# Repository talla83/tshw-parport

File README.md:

lsrio16 für Tom simple handwheel -
Eine kleine Erweiterungsplatine mit universellen IOs.

16 x digital output 16 x digital input 

Schnittstelle = Parallel Port oder andere mit GPIO

Der Encoder muss direkt an den ParPort angeschlossen.

http://wiki.linuxcnc.org/cgi-bin/wiki.pl?Shift_Register_Port_Expander

https://www.thingiverse.com/thing:3684937

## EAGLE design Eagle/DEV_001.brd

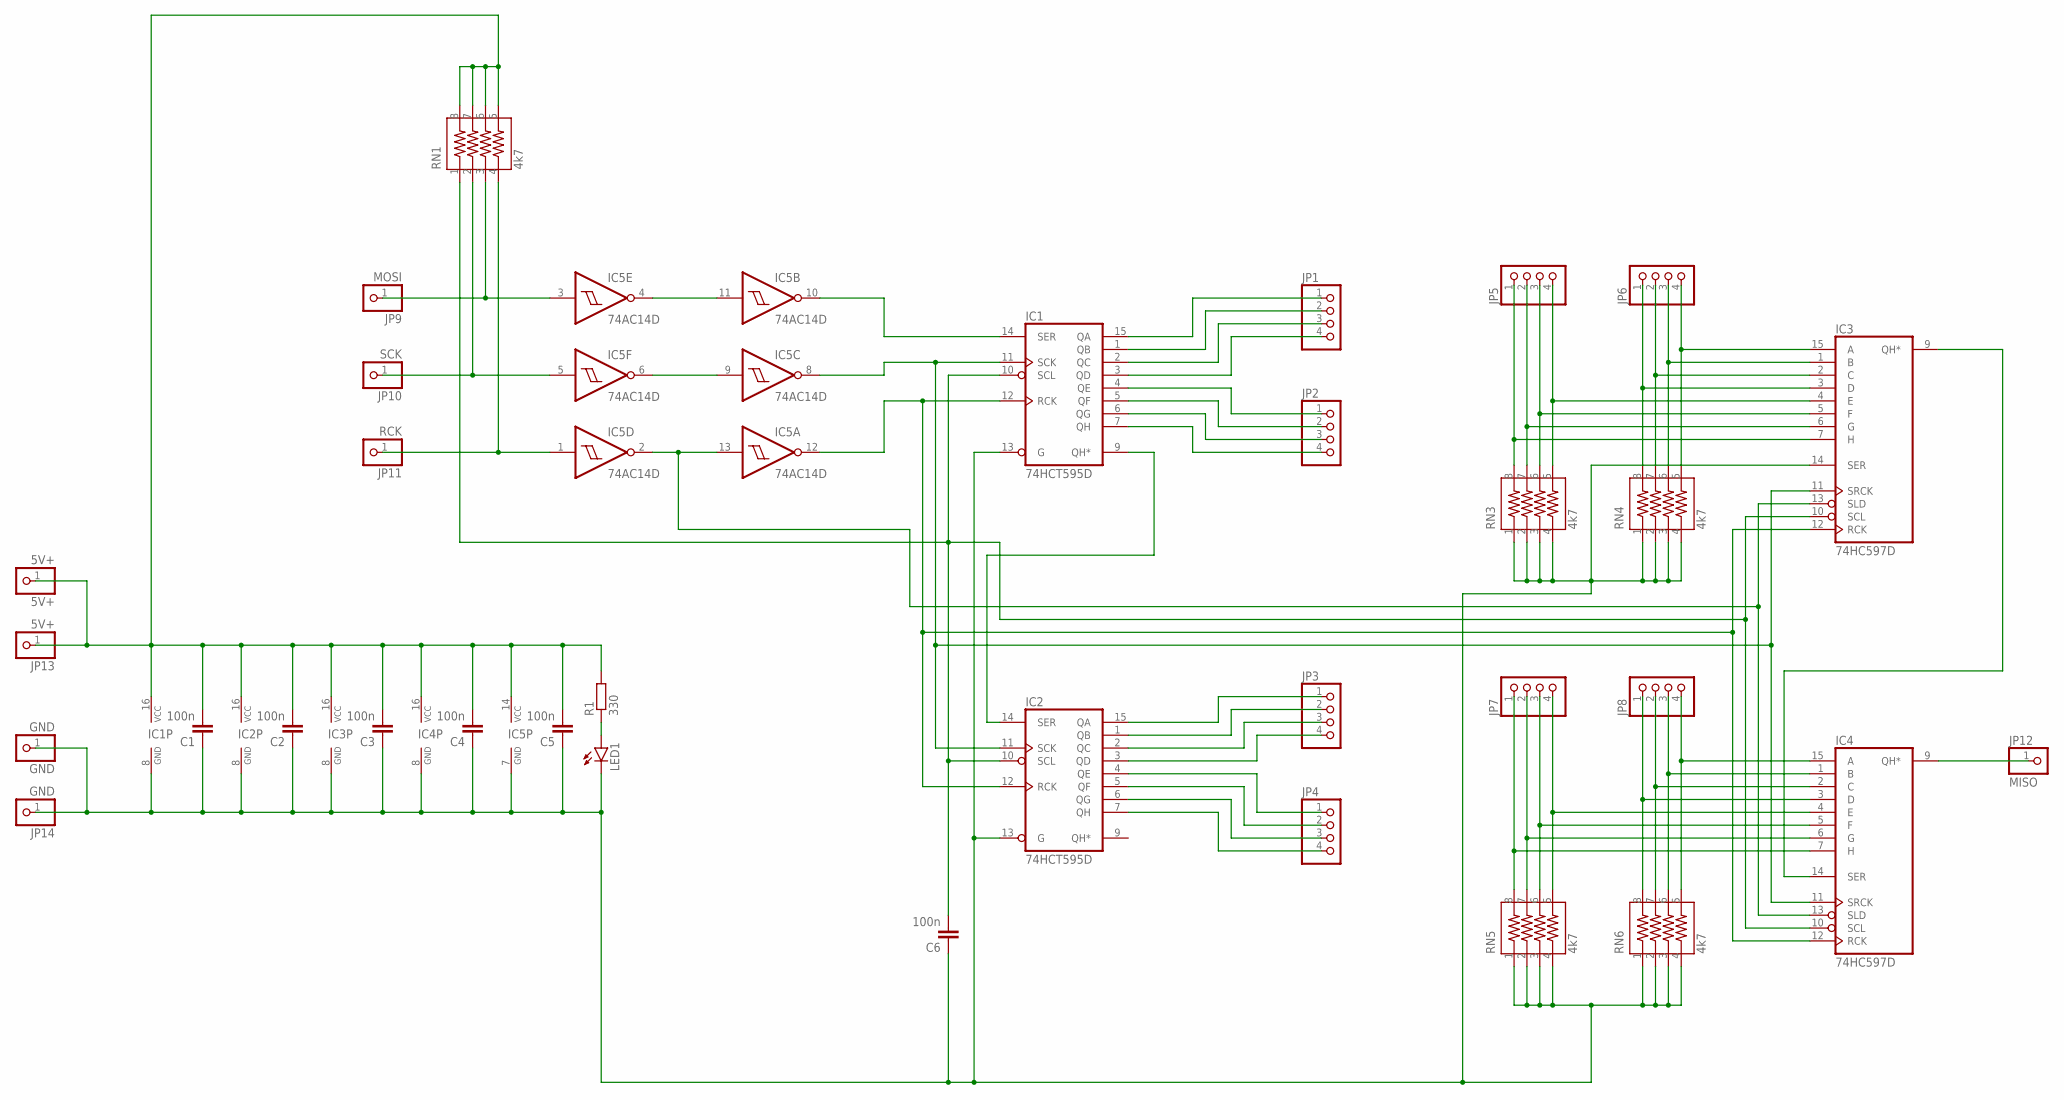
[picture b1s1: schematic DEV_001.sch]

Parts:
5V+: 5V+; 1X01
C1, C2, C3, C4, C5, C6: 100n; C1206K
GND: GND; 1X01
IC1, IC2: 74HCT595D; SO16
IC3, IC4: 74HC597D; SO16
IC5: 74AC14D; SO14
JP1, JP2, JP3, JP4, JP5, JP6, JP7, JP8: PINHD-1X4; 1X04
JP9: MOSI; 1X01
JP10: SCK; 1X01
JP11: RCK; 1X01
JP12: MISO; 1X01
JP13: 5V+; 1X01
JP14: GND; 1X01
LED1: LEDCHIPLED_0805; CHIPLED_0805
R1: 330; R1206
RN1, RN3, RN4, RN5, RN6: 4k7; 742C083103JP

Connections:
unnamed: IC5.4 (O), IC5.11 (I)
unnamed: IC5.6 (O), IC5.9 (I)
unnamed: IC5.3 (I), JP9.1, RN1.3
unnamed: IC5.5 (I), JP10.1, RN1.2
unnamed: IC5.1 (I), JP11.1, RN1.4
unnamed: 5V+.1, C1.2, C2.2, C3.2, C4.2, C5.2, IC1.16 (VCC), IC2.16 (VCC), IC3.16 (VCC), IC4.16 (VCC), IC5.14 (VCC), JP13.1, R1.2, RN1.5, RN1.6, RN1.7, RN1.8
unnamed: IC1.14 (SER), IC5.10 (O)
unnamed: C1.1, C2.1, C3.1, C4.1, C5.1, C6.1, GND.1, IC1.8 (GND), IC1.13 (G), IC2.8 (GND), IC2.13 (G), IC3.8 (GND), IC3.14 (SER), IC4.8 (GND), IC5.7 (GND), JP14.1, LED1.C, RN3.1, RN3.2, RN3.3, RN3.4, RN4.1, RN4.2, RN4.3, RN4.4, RN5.1, RN5.2, RN5.3, RN5.4, RN6.1, RN6.2, RN6.3, RN6.4
unnamed: IC1.15 (QA), JP1.1
unnamed: IC1.1 (QB), JP1.2
unnamed: IC1.2 (QC), JP1.3
unnamed: IC1.3 (QD), JP1.4
unnamed: IC1.4 (QE), JP2.1
unnamed: IC1.5 (QF), JP2.2
unnamed: IC1.6 (QG), JP2.3
unnamed: IC1.7 (QH), JP2.4
unnamed: IC1.9 (QH*), IC2.14 (SER)
unnamed: IC2.15 (QA), JP3.1
unnamed: IC2.1 (QB), JP3.2
unnamed: IC2.2 (QC), JP3.3
unnamed: IC2.3 (QD), JP3.4
unnamed: IC2.4 (QE), JP4.1
unnamed: IC2.5 (QF), JP4.2
unnamed: IC2.6 (QG), JP4.3
unnamed: IC2.7 (QH), JP4.4
unnamed: IC3.9 (QH*), IC4.14 (SER)
unnamed: IC4.9 (QH*), JP12.1
unnamed: IC3.7 (H), JP5.1, RN3.8
unnamed: IC3.6 (G), JP5.2, RN3.7
unnamed: IC3.5 (F), JP5.3, RN3.6
unnamed: IC3.4 (E), JP5.4, RN3.5
unnamed: IC3.3 (D), JP6.1, RN4.8
unnamed: IC3.2 (C), JP6.2, RN4.7
unnamed: IC3.1 (B), JP6.3, RN4.6
unnamed: IC3.15 (A), JP6.4, RN4.5
unnamed: IC1.11 (SCK), IC2.11 (SCK), IC3.11 (SRCK), IC4.11 (SRCK), IC5.8 (O)
unnamed: IC3.13 (SLD), IC4.13 (SLD), IC5.2 (O), IC5.13 (I)
unnamed: IC1.12 (RCK), IC2.12 (RCK), IC3.12 (RCK), IC4.12 (RCK), IC5.12 (O)
unnamed: IC4.7 (H), JP7.1, RN5.8
unnamed: IC4.6 (G), JP7.2, RN5.7
unnamed: IC4.5 (F), JP7.3, RN5.6
unnamed: IC4.4 (E), JP7.4, RN5.5
unnamed: IC4.3 (D), JP8.1, RN6.8
unnamed: IC4.2 (C), JP8.2, RN6.7
unnamed: IC4.1 (B), JP8.3, RN6.6
unnamed: IC4.15 (A), JP8.4, RN6.5
unnamed: LED1.A, R1.1
unnamed: C6.2, IC1.10 (SCL), IC2.10 (SCL), IC3.10 (SCL), IC4.10 (SCL), RN1.1

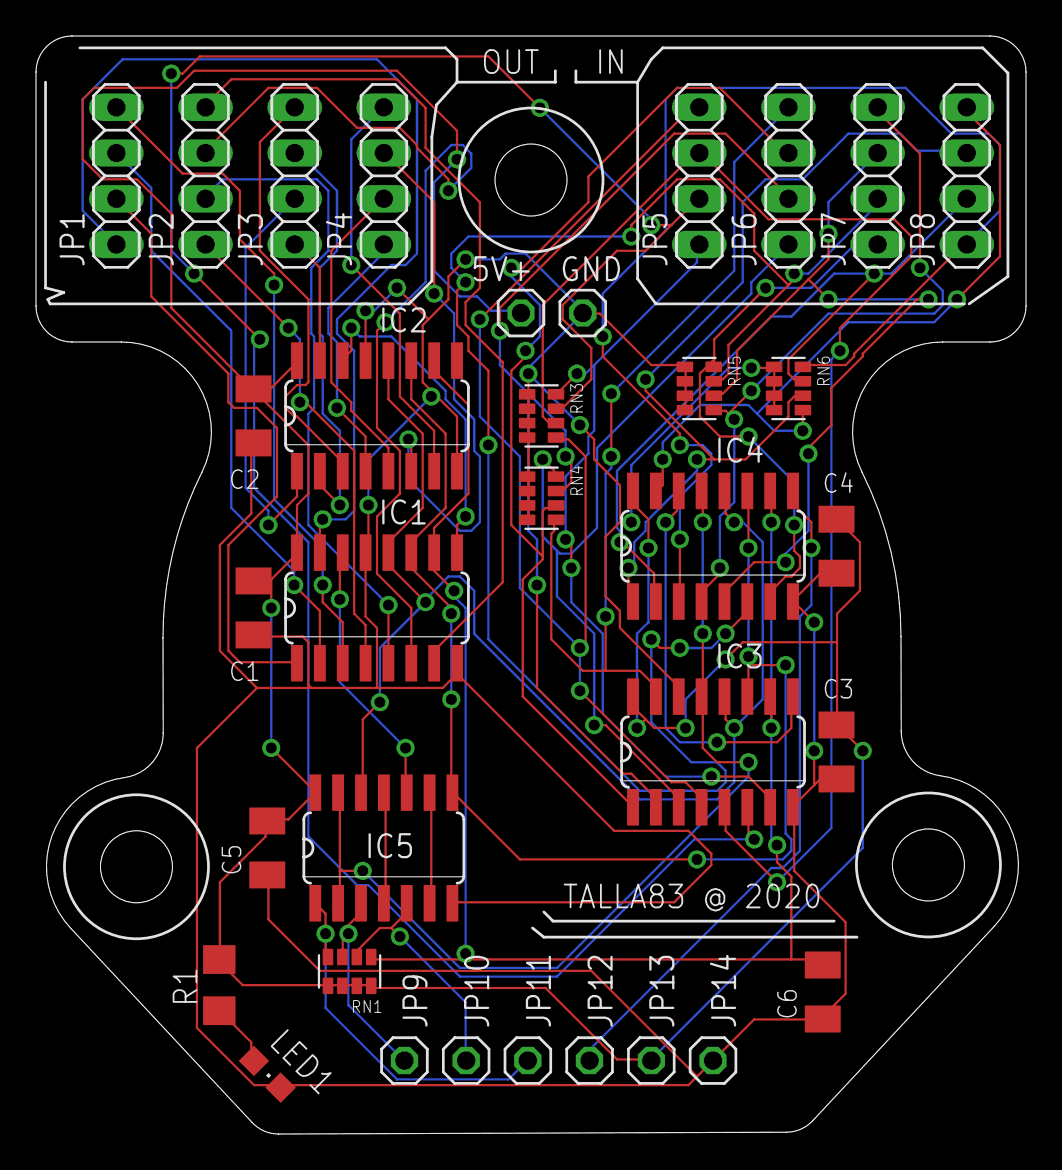
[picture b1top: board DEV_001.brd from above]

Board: 2 copper layers, 55.0 x 61.0 mm, 34 parts (0 on the bottom side), 48 nets.
